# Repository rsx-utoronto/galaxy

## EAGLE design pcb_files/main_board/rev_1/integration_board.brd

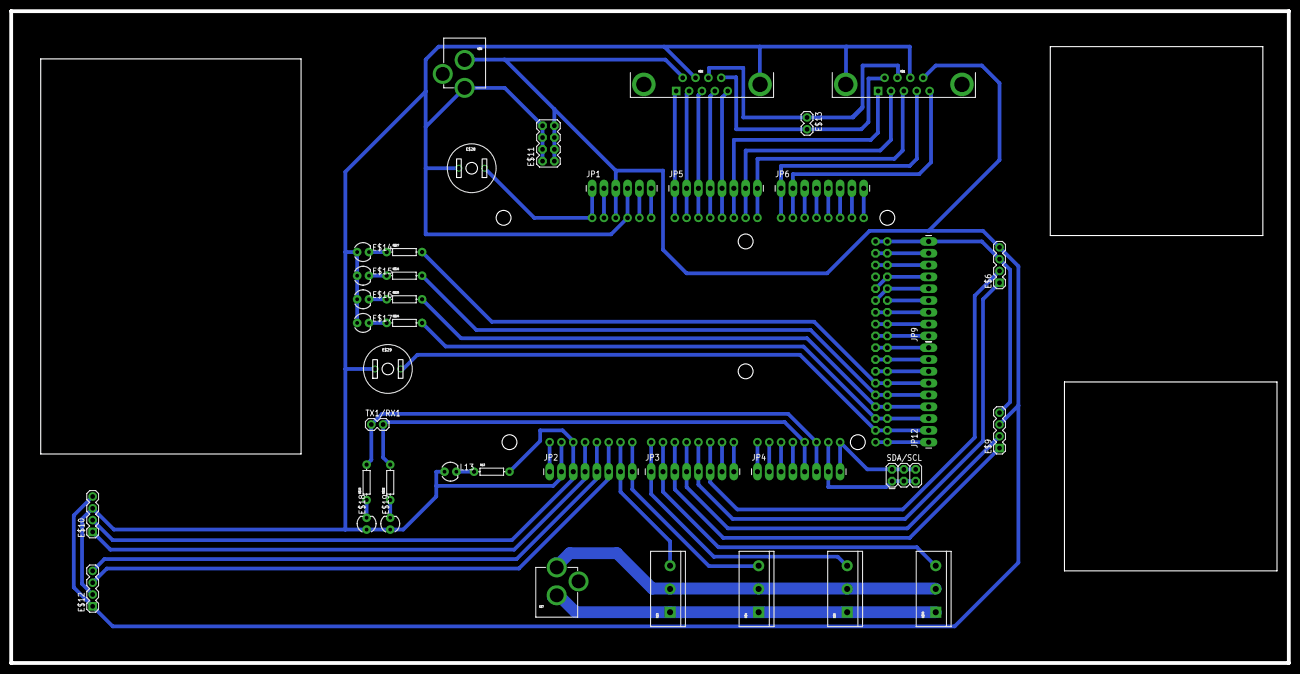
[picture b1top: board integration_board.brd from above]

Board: 2 copper layers, 274.8 x 140.2 mm, 41 parts (1 on the bottom side), 72 nets.

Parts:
E$1, E$2: DB9
E$3, E$4, E$5, E$30: SCREWTERMINAL-5MM-3
E$6, E$9, E$10, E$12: 1X04
E$7, E$8: POWER_JACK_PTH
E$11: 2X4
E$13: 1X02
E$14, E$15, E$16, E$17, E$18, E$19: LED3MM
E$22, E$23, E$24, E$25, E$26, E$27: AXIAL-0.3
E$28, E$29: BUTTON-10MM
JP1: 1X06_LONGPADS
JP2, JP3, JP4, JP5, JP6: 1X08_LONGPADS
JP9, JP12: 1X09_LONGPADS
L13: LED3MM
R13: AXIAL-0.3
SDA/SCL: 2X3
TX1/RX1: 1X02
U1: ARDUINO-MEGAFULL; ARDUINO_MEGA

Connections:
S$1: JP1.1, U1.RESET
S$2: JP1.2, U1.3.3V
S$3: E$10.3, E$11.2, E$11.4, E$11.6, E$11.8, E$12.2, E$14.A, E$15.A, E$16.A, E$17.A, E$18.A, E$19.A, JP1.4, JP2.2, L13.A, U1.GND@0, U1.GND@4
S$5: JP1.5, U1.GND@1
S$6: JP1.6, U1.VIN
S$7: JP5.1, U1.A0
S$8: JP5.2, U1.A1
S$9: JP5.3, U1.A2
S$10: JP5.4, U1.A3
S$11: JP5.5, U1.A4
S$12: E$6.3, E$9.4
S$13: JP5.7, U1.A6
S$14: JP5.6, U1.A5
S$17: JP6.3, U1.A10
S$18: JP6.4, U1.A11
S$19: JP6.5, U1.A12
S$20: JP6.6, U1.A13
S$21: JP6.7, U1.A14
S$22: JP6.8, U1.A15
S$23: JP2.6, U1.10
S$26: E$3.1, E$30.1
S$27: JP2.4, U1.12
S$28: JP2.7, U1.9
S$29: JP2.1, U1.AREF
S$31: JP2.5, U1.11
S$33: E$9.1, JP3.3, U1.5
S$34: E$9.2, JP3.4, U1.4
S$35: E$6.1, JP3.5, U1.3
S$36: E$6.2, JP3.6, U1.2
S$37: JP2.8, U1.8
S$39: JP4.1, U1.14
S$40: JP4.2, U1.15
S$41: JP4.3, U1.16
S$42: JP4.4, U1.17
S$43: E$22.P$2, JP4.5, TX1/RX1.2, U1.18
S$44: E$23.P$2, JP4.6, TX1/RX1.1, U1.19
S$45: JP4.7, SDA/SCL.1, SDA/SCL.5, U1.20
S$46: JP4.8, SDA/SCL.2, SDA/SCL.6, U1.21
S$47: E$27.P$2, JP12.6, U1.30
S$48: JP12.2, U1.22
S$49: E$24.P$2, JP12.3, U1.24
S$50: E$25.P$2, JP12.4, U1.26
S$51: E$26.P$2, JP12.5, U1.28
S$53: JP12.7, U1.32
S$54: JP12.8, U1.34
S$55: JP12.9, U1.36
S$56: JP9.1, U1.38
S$57: JP9.2, U1.40
S$58: JP9.3, U1.42
S$59: JP9.7, U1.50
S$60: JP9.8, U1.52
S$62: JP9.6, U1.46
S$63: JP9.5, U1.44
S$64: JP9.4, U1.45
S$67: JP9.9, U1.GND@2
S$68: JP3.7, U1.1
S$72: JP12.1, U1.5V@1
S$73: JP3.8, U1.0
S$74: E$14.K, E$27.P$1
S$75: E$15.K, E$26.P$1
S$76: E$16.K, E$25.P$1
S$77: E$17.K, E$24.P$1
S$78: E$18.K, E$23.P$1
S$79: E$19.K, E$22.P$1
S$80: L13.K, R13.P$1
S$82: JP6.1, U1.A8
S$83: JP3.1, U1.7
S$84: JP3.2, U1.6
S$85: JP2.3, U1.13
S$86: JP5.8, U1.A7
S$95: E$6.4, E$9.3, E$10.4, E$11.1, E$11.3, E$11.5, E$11.7, E$12.1, JP1.3, U1.5V@0
S$97: JP6.2, U1.A9

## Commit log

2015-04-13 added dirs
2015-04-13 added notes
2015-04-13 Jeff is testing github on windows
    blah blah blah
2015-04-13 Deleted test file
2015-04-13 added notes on using github windows app
2015-04-14 Added more stuff to board layout
    Added leds, buttons, resistors, rerouted some wires, added some pwm for
    main motor drivers
2015-04-14 Added SDA/SCL pins, rerouted a lot of wires
    Still not finished
2015-04-15 Finished routing wires, added outline
    Drill holes still need to be added I think
2015-04-15 Edited board layout
    Added I2C pins for db9s to make connecting easier. Will need a jumper
    wire to connect i2c of db9s to the arduino.
2015-04-18 desert scale testing
2015-04-18 desert scale image
2015-04-18 control by keyboard
2015-04-18 added block diagram for rover systems
2015-04-18 joystick control
2015-04-18 First Edit
2015-04-18 Sensor board schematic and board files
2015-04-18 Arduino Parallel Port Wiring Link for CNC
2015-04-18 ran pcb-gcode
2015-04-20 Updated Integration Board
    Moved all traces to bottom layer
2015-04-21 Integration_board_update
2015-04-21 Sensor_board_update
2015-04-21 Added serial protocols into rover/mcu.
    These provide a communication standard. See the readme in rover/mcu for more information. Also added a gitignore.
2015-04-25 Tested GPS at UTIAS
2015-04-25 user input astronauts feature
2015-04-25 Sensor_board and Main Board Update
2015-04-25 Added wider traces to main board
    Some traces conflict however.
2015-04-30 added rover server code
2015-04-30 added ground station client code
2015-04-30 Update to sensor board
    Board now contains, 3x gas sensor, 1 compass, 1 pressure sensor, 1 rain
    sensor, 1 accelerometer.
2015-05-02 MotorFunction
2015-05-02 MotorFunction adjusted with joystick value
2015-05-02 MotorFunction two wheels
2015-05-02 i2c connection between Arduino and RPi
2015-05-02 motor function with comments
2015-05-02 sorting data from pi to arduino
2015-05-02 added sample network chat code for testing with pi
2015-05-02 controller code
2015-05-02 lots of frustration with 2 way, leaving it at one way network comm for now
2015-05-07 updated sorting data
2015-05-07 move files to the correct folders
2015-05-07 telnet, server, motor control, arduino/pi interface, etc.
2015-05-10 update sorting data ...
2015-05-10 Combined string parse code with motor pwm code
2015-05-12 Reduced sensitivity for rotation on spot
2015-05-14 arm added
2015-05-16 gps with four to five reference point tested at utias
2015-05-16 fixed motor problem+ added the claw
2015-05-17 obc server code update
2015-05-17 updated gps
2015-05-17 rpi sending gps
2015-05-17 arduino file
2015-05-21 updated rover
2015-05-22 gps sending
2015-05-22 sensorSending
2015-05-22 sensor receiver
2015-05-23 3 gas sensors + 2 soil mosture sensors
2015-05-23 changed speed of the claw
2015-05-23 move to correct folder
2015-05-23 compass only
2015-05-23 final code for arduino
2015-05-23 rename
2015-05-23 organize
2015-05-23 combined sensors and gps
2015-05-23 Comments for IP address configuration
2015-05-23 Commented IP configuration
2015-05-23 Commented piSending.py
2015-05-23 Updated sensorSending.py
2015-05-23 Modified name of variable
2015-05-23 sensor code
2015-05-23 samsh
2015-05-24 updatde
2015-05-24 arrow rotation
2015-05-27 adding two more signals for the motors
2015-05-27 Updated Arduino code with different forward/backward motors and compass values
2015-05-27 Added variable forward/backward motors and compass sending to RPi
2015-05-28 working in the hotel
2015-05-28 Updated with GPS map display
2015-05-28 version 2
2015-05-29 Arduino Final Func with/without sensors/actuators
2015-05-30 new gps
2015-05-30 testing file
2015-05-30 region image
2015-05-30 astronaut
2015-05-30 astronaut feature
2015-05-30 more label
2015-08-01 motordriver documentation

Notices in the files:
parts and their libraries:
SparkFun-Boards: Licensing: Creative Commons ShareAlike 4.0 International - https://creativecommons.org/licenses/by-sa/4.0
